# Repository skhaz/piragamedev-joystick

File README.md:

[Slides](https://speakerdeck.com/skhaz/como-criar-o-seu-proprio-joystick)

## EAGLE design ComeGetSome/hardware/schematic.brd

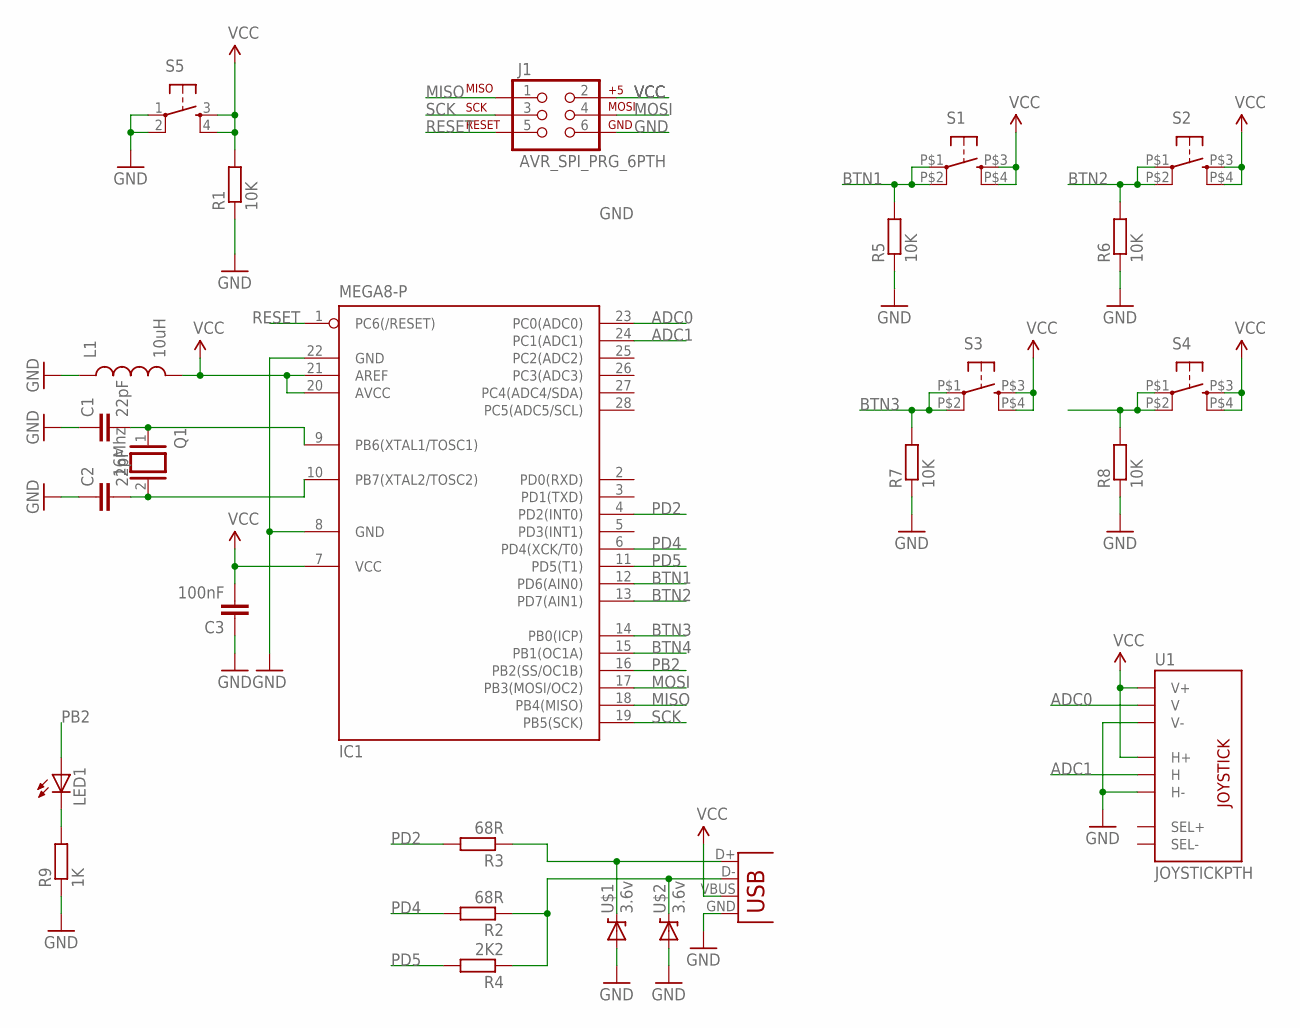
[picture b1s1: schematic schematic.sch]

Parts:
C1, C2: 22pF; CAP-PTH-SMALL-KIT
C3: 100nF; CAP-PTH-SMALL-KIT
IC1: MEGA8-P; DIL28-3
J1: AVR_SPI_PRG_6PTH; 2X3
L1: 10uH; AXIAL-0.6
LED1: LED3MM
Q1: 16Mhz; Q
R1, R5, R6, R7, R8: 10K; 0204/7
R2, R3: 68R; 0204/7
R4: 2K2; 0204/7
R9: 1K; 0204/7
S1, S2, S3, S4: TAC_SWITCHKSA_SEALED; KSA_SEALED_TAC_SWITCH
S5: TAC_SWITCHPTH; TACTILE-PTH
U1: JOYSTICKPTH; JOYSTICK
U$1, U$2: 3.6v; DIODE-ZENER
X1: USBPTH-VERTICAL; USB-B-PTH-VERTICAL

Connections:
ADC0: IC1.23 (PC0(ADC0)), U1.V2 (V)
ADC1: IC1.24 (PC1(ADC1)), U1.H2 (H)
BTN1: IC1.12 (PD6(AIN0)), R5.2, S1.P$1 (1), S1.P$2 (2)
BTN2: IC1.13 (PD7(AIN1)), R6.2, S2.P$1 (1), S2.P$2 (2)
BTN3: IC1.14 (PB0(ICP)), R7.2, S3.P$1 (1), S3.P$2 (2)
BTN4: IC1.15 (PB1(OC1A)), R8.2, S4.P$1 (1), S4.P$2 (2)
GND: C1.1, C2.1, C3.1, IC1.8 (GND), IC1.22 (GND), J1.6, L1.P$1 (1), R1.1, R5.1, R6.1, R7.1, R8.1, R9.1, S5.1, S5.2, U1.H3 (H-), U1.V3 (V-), U$1.P$2 (A), U$2.P$2 (A), X1.GND
MISO: IC1.18 (PB4(MISO)), J1.1
MOSI: IC1.17 (PB3(MOSI/OC2)), J1.4
unnamed: C1.2, IC1.9 (PB6(XTAL1/TOSC1)), Q1.1
unnamed: C2.2, IC1.10 (PB7(XTAL2/TOSC2)), Q1.2
unnamed: R3.1, U$1.P$1 (C), X1.D+
unnamed: LED1.K (C), R9.2
unnamed: R2.1, R4.1, U$2.P$1 (C), X1.D-
PB2: IC1.16 (PB2(SS/OC1B)), LED1.A
PD2: IC1.4 (PD2(INT0)), R3.2
PD4: IC1.6 (PD4(XCK/T0)), R2.2
PD5: IC1.11 (PD5(T1)), R4.2
RESET: IC1.1 (PC6(/RESET)), J1.5
SCK: IC1.19 (PB5(SCK)), J1.3
VCC: C3.2, IC1.7 (VCC), IC1.20 (AVCC), IC1.21 (AREF), J1.2, L1.P$2 (2), R1.2, S1.P$3 (3), S1.P$4 (4), S2.P$3 (3), S2.P$4 (4), S3.P$3 (3), S3.P$4 (4), S4.P$3 (3), S4.P$4 (4), S5.3, S5.4, U1.H1 (H+), U1.V1 (V+), X1.VBUS

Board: 2 copper layers, 26 parts (0 on the bottom side), 21 nets, no tracks yet.

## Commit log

2013-07-02 First blood!
2022-11-05 Optimize images

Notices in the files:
parts and their libraries:
SparkFun: Licensing: CC v3.0 Share-Alike You are welcome to use this library for commercial purposes.
